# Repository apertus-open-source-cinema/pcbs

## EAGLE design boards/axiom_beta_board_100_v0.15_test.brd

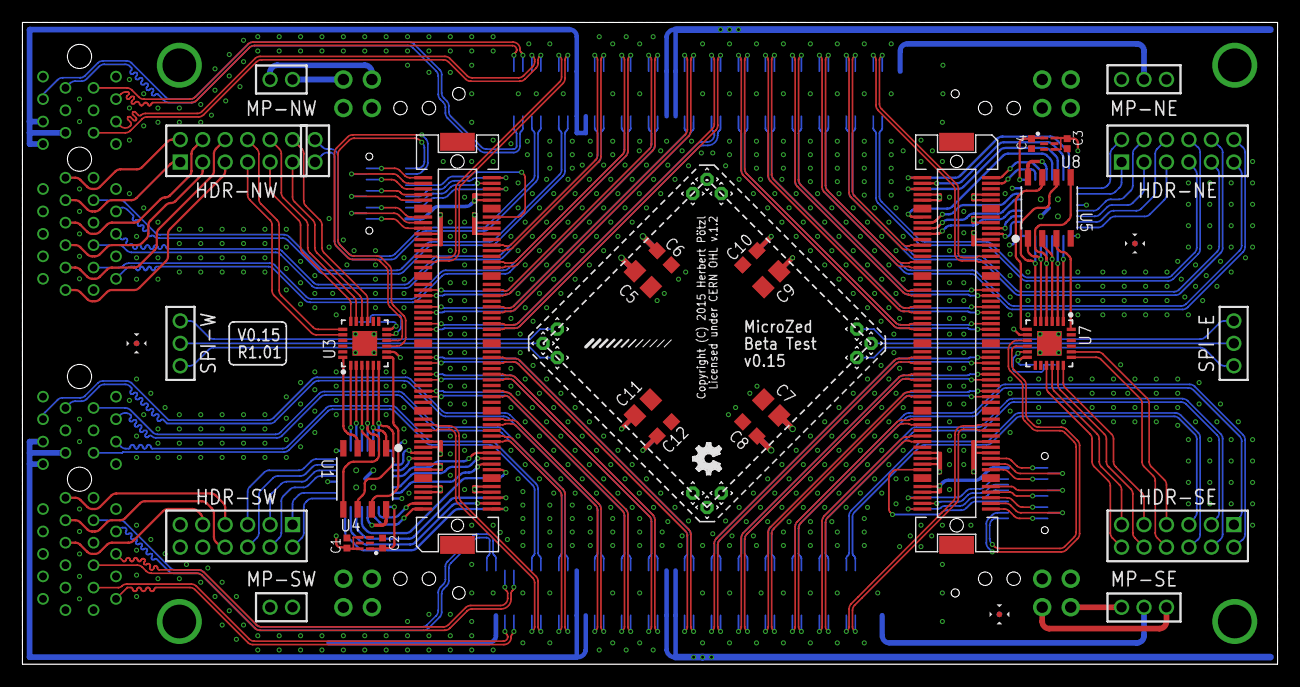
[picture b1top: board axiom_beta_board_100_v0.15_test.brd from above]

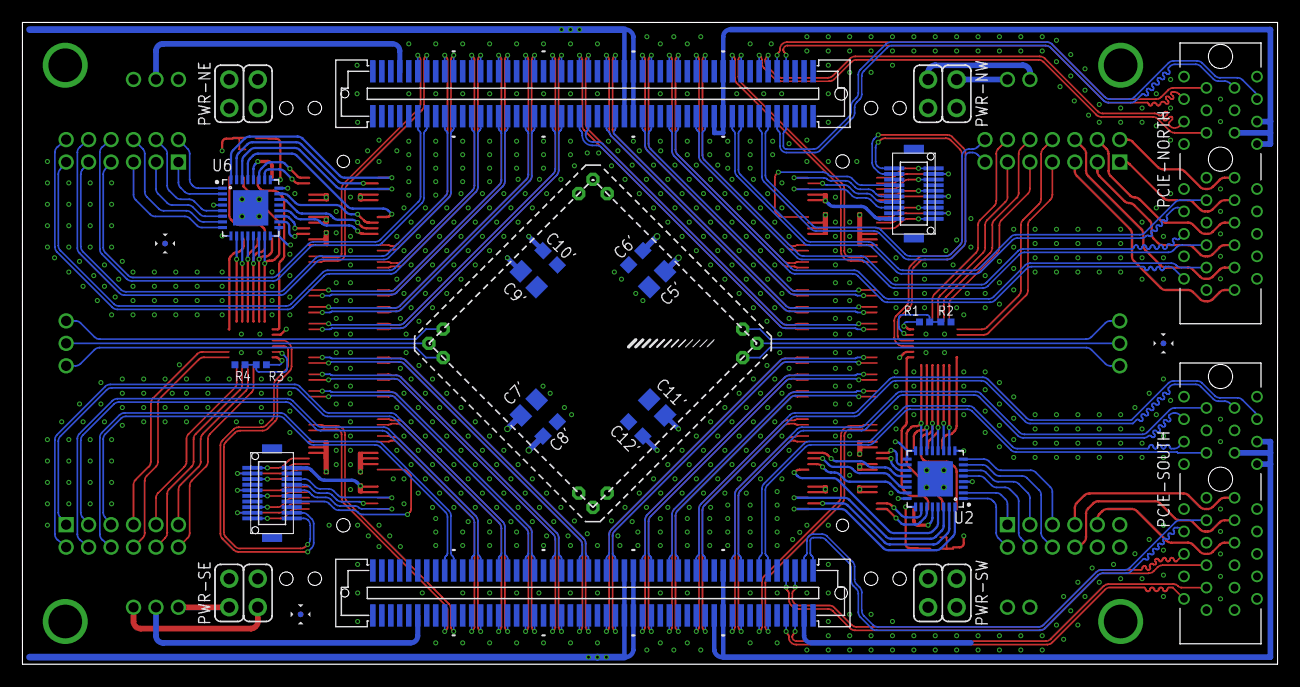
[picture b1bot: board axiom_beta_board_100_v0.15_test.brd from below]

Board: 4 copper layers, 111.8 x 57.1 mm, 67 parts (23 on the bottom side), 247 nets.

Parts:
C1, C2, C3, C4: 0402-B
C5, C5', C7, C7', C9, C9', C11, C11': 0805-A
C6, C6', C8, C8', C10, C10', C12, C12': 0603-A
HDR-NE: 2X06M
HDR-NW: 2X06M
HDR-SE: 2X06M
HDR-SW: 2X06M
LOGO1: OSHW_LOGO_FILLX0100-NT; OSHW_FILLX100_NOTEXT
M-LVDS: 1X02M
MP-NE: 1X03M
MP-NW: 1X02M
MP-SE: 1X03M
MP-SW: 1X02M
PB-NW: DF12(XX)-20DP-0.5V
PB-SE: DF12(XX)-20DP-0.5V
PCIE-NORTH: PCIE-36SOCKET; PCIE-36
PCIE-SOUTH: PCIE-36SOCKET; PCIE-36
PWR-NE: PINHD-2X02_2.54; 2X02
PWR-NW: PINHD-2X02_2.54; 2X02
PWR-SE: PINHD-2X02_2.54; 2X02
PWR-SW: PINHD-2X02_2.54; 2X02
R1, R2, R3, R4: 0402-B
SPI-E: PINHD-2X02_2.00; 1X03M
SPI-W: PINHD-2X02_2.00; 1X03M
U1, U5: SST25VF020B; SOIC127P600X175-8N
U2, U6: ICE40_LP384-SG32; QFN-32
U3, U7: MCP23018QFN; QFN50P400X400X80-25N
U4, U8: LD6806F; DFN100X150X50-6N
U$1, U$2, U$11, U$14, U$15, U$16, U$17, U$18, U$19, U$20, U$21, U$22: PINPAD1.27MM; 1.2/0.6
X-EAST: FX10-100/10S; FX10A-100S/10
X-WEST: FX10-100/10S; FX10A-100S/10
ZED1: µZ-FCI-NOHOLES; µZ-NOHOLES

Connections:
!HOLD!_N: U5.7, U7.7
!HOLD!_S: U1.7, U3.7
!WP!_N: U5.3, U7.24
!WP!_SW: U1.3, U3.24
A_SCL: PB-SE.1, U7.9
A_SDA: PB-SE.3, U7.10
BANK13_00_N: PCIE-NORTH.A14, ZED1.89
BANK13_00_P: PCIE-NORTH.A13, ZED1.87
BANK13_01_N: M-LVDS.1, ZED1.90
BANK13_01_P: M-LVDS.2, ZED1.88
BANK13_02_N: PCIE-NORTH.A16, ZED1.93
BANK13_02_P: PCIE-NORTH.A17, ZED1.91
BANK13_03_N: PCIE-NORTH.B16, ZED1.94
BANK13_03_P: PCIE-NORTH.B17, ZED1.92
BANK13_04_N: PCIE-SOUTH.A6, ZED1.195
BANK13_04_P: PCIE-SOUTH.A5, ZED1.193
BANK13_05_N: PCIE-SOUTH.A3, ZED1.196
BANK13_05_P: PCIE-SOUTH.A2, ZED1.194
BANK13_06_N: PCIE-SOUTH.A8, ZED1.199
BANK13_06_P: PCIE-SOUTH.A9, ZED1.197
B_SCL: PB-NW.1, U3.9
B_SDA: PB-NW.3, U3.10
CDONE_N: U6.11, U7.2
CDONE_S: U2.11, U3.2
CRESET_N: U6.10, U7.1
CRESET_S: U2.10, U3.1
C_CK_E: SPI-E.2, U$14.1
C_CK_W: SPI-W.2, U$1.1
C_SI_E: SPI-E.1, U$15.1
C_SI_W: SPI-W.1, U$2.1
C_SO_E: SPI-E.3, U$16.1
C_SO_W: SPI-W.3, U$11.1
E_EN: U6.23, X-EAST.14
E_I2C_V: PWR-NE.1, X-EAST.11, X-EAST.13
E_SCK: U6.29, X-EAST.12
E_SCL: U6.19, X-EAST.15
E_SDA: U6.18, X-EAST.17
E_SDI: U6.22, X-EAST.16
E_SDI_V: PWR-NE.3, X-EAST.19, X-EAST.21
E_SDO: U6.20, X-EAST.18
E_VE: PWR-SE.1, X-EAST.79, X-EAST.81, X-EAST.83, X-EAST.84, X-EAST.86, X-EAST.88
E_VE_CV: PB-SE.7, X-EAST.90
E_VE_OV: PB-SE.10, X-EAST.93
E_VE_UV: PB-SE.12, X-EAST.91
GND: C1.2, C2.2, C3.2, C4.2, C5.2, C5'.2, C6.2, C6'.2, C7.2, C7'.2, C8.2, C8'.2, C9.2, C9'.2, C10.2, C10'.2, C11.2, C11'.2, C12.2, C12'.2, MP-NE.1, MP-NE.3, MP-SW.1, MP-SW.2, PB-NW.5, PB-NW.8, PB-NW.9, PB-NW.14, PB-NW.17, PB-SE.5, PB-SE.8, PB-SE.9, PB-SE.14, PB-SE.17, PCIE-NORTH.A1, PCIE-NORTH.A4, PCIE-NORTH.A7, PCIE-NORTH.A10, PCIE-NORTH.A12, PCIE-NORTH.A15, PCIE-NORTH.A18, PCIE-NORTH.B15, PCIE-NORTH.B18, PCIE-SOUTH.A1, PCIE-SOUTH.A4, PCIE-SOUTH.A7, PCIE-SOUTH.A10, PCIE-SOUTH.A12, PCIE-SOUTH.A15, PCIE-SOUTH.A18, PCIE-SOUTH.B15, PCIE-SOUTH.B18, R2.2, R4.2, U1.4, U2.3, U2.21, U2.EP, U3.23, U4.3, U5.4, U6.3, U6.21, U6.EP, U7.23, U8.3, U$17.1, U$20.1, X-EAST.5, X-EAST.20, X-EAST.23, X-EAST.26, X-EAST.29, X-EAST.31, X-EAST.32, X-EAST.37, X-EAST.38, X-EAST.43, X-EAST.44, X-EAST.49, X-EAST.50, X-EAST.51, X-EAST.52, X-EAST.57, X-EAST.58, X-EAST.63, X-EAST.64, X-EAST.69, X-EAST.70, X-EAST.71, X-EAST.76, X-EAST.77, X-EAST.82, X-EAST.G1, X-EAST.G2, X-EAST.G3, X-EAST.G4, X-EAST.G5, X-EAST.G6, X-EAST.G7, X-EAST.G8, X-EAST.G9, X-EAST.G10, X-WEST.5, X-WEST.20, X-WEST.23, X-WEST.26, X-WEST.29, X-WEST.31, X-WEST.32, X-WEST.37, X-WEST.38, X-WEST.43, X-WEST.44, X-WEST.49, X-WEST.50, X-WEST.51, X-WEST.52, X-WEST.57, X-WEST.58, X-WEST.63, X-WEST.64, X-WEST.69, X-WEST.70, X-WEST.71, X-WEST.76, X-WEST.77, X-WEST.82, X-WEST.G1, X-WEST.G2, X-WEST.G3, X-WEST.G4, X-WEST.G5, X-WEST.G6, X-WEST.G7, X-WEST.G8, X-WEST.G9, X-WEST.G10, ZED1.15, ZED1.16, ZED1.21, ZED1.22, ZED1.27, ZED1.28, ZED1.33, ZED1.34, ZED1.39, ZED1.40, ZED1.45, ZED1.46, ZED1.51, ZED1.52, ZED1.65, ZED1.66, ZED1.71, ZED1.72, ZED1.77, ZED1.85, ZED1.86, ZED1.95, ZED1.96, ZED1.115, ZED1.116, ZED1.121, ZED1.122, ZED1.127, ZED1.128, ZED1.133, ZED1.134, ZED1.139, ZED1.140, ZED1.145, ZED1.146, ZED1.151, ZED1.152, ZED1.165, ZED1.166, ZED1.171, ZED1.172, ZED1.177, ZED1.185, ZED1.186, ZED1.191, ZED1.192
GPA0_E: HDR-SE.12, U7.15
GPA0_W: HDR-NW.12, U3.15
GPA1_E: HDR-SE.11, U7.16
GPA1_W: HDR-NW.11, U3.16
GPA2_E: HDR-SE.10, U7.17
GPA2_W: HDR-NW.10, U3.17
GPA3_E: HDR-SE.9, U7.18
GPA3_W: HDR-NW.9, U3.18
GPA4_E: HDR-SE.8, U7.19
GPA4_W: HDR-NW.8, U3.19
GPA5_E: HDR-SE.7, U7.20
GPA5_W: HDR-NW.7, U3.20
IOL_2A_N: HDR-NE.1, U6.2
IOL_2A_S: HDR-SW.1, U2.2
IOL_2B_N: HDR-NE.2, U6.1
IOL_2B_S: HDR-SW.2, U2.1
IOL_4A_N: HDR-NE.4, U6.5
IOL_4A_S: HDR-SW.4, U2.5
IOL_4B_N: HDR-NE.3, U6.6
IOL_4B_S: HDR-SW.3, U2.6
IOL_5A_N: HDR-NE.5, U6.8
IOL_5A_S: HDR-SW.5, U2.8
IOL_5B_N: HDR-NE.6, U6.7
IOL_5B_S: HDR-SW.6, U2.7
JTAG_V: PWR-SW.3, X-WEST.19, X-WEST.21
JX1_00_N: X-EAST.27, ZED1.13
JX1_00_P: X-EAST.25, ZED1.11
JX1_01_N: HDR-NE.8, ZED1.14
JX1_01_P: HDR-NE.7, ZED1.12
JX1_02_N: X-EAST.24, ZED1.19
JX1_02_P: X-EAST.22, ZED1.17
JX1_03_N: HDR-NE.10, ZED1.20
JX1_03_P: HDR-NE.9, ZED1.18
JX1_04_N: X-EAST.30, ZED1.25
JX1_04_P: X-EAST.28, ZED1.23
JX1_05_N: HDR-NE.12, ZED1.26
JX1_05_P: HDR-NE.11, ZED1.24
JX1_06_N: X-EAST.36, ZED1.31
JX1_06_P: X-EAST.34, ZED1.29
JX1_07_N: X-EAST.35, ZED1.32
JX1_07_P: X-EAST.33, ZED1.30
JX1_08_N: X-EAST.42, ZED1.37
JX1_08_P: X-EAST.40, ZED1.35
JX1_09_N: X-EAST.41, ZED1.38
JX1_09_P: X-EAST.39, ZED1.36
JX1_10_N: X-EAST.48, ZED1.43
JX1_10_P: X-EAST.46, ZED1.41
JX1_11_N: X-EAST.47, ZED1.44
JX1_11_P: X-EAST.45, ZED1.42
JX1_12_N: X-WEST.56, ZED1.49
JX1_12_P: X-WEST.54, ZED1.47
JX1_13_N: X-WEST.55, ZED1.50
JX1_13_P: X-WEST.53, ZED1.48
JX1_14_N: X-WEST.62, ZED1.55
JX1_14_P: X-WEST.60, ZED1.53
JX1_15_N: X-WEST.61, ZED1.56
JX1_15_P: X-WEST.59, ZED1.54
JX1_16_N: X-WEST.68, ZED1.63
JX1_16_P: X-WEST.66, ZED1.61
JX1_17_N: X-WEST.67, ZED1.64
JX1_17_P: X-WEST.65, ZED1.62
JX1_18_N: X-WEST.74, ZED1.69
JX1_18_P: X-WEST.72, ZED1.67
JX1_19_N: PCIE-NORTH.A3, ZED1.70
JX1_19_P: PCIE-NORTH.A2, ZED1.68
JX1_20_N: X-WEST.80, ZED1.75
JX1_20_P: X-WEST.78, ZED1.73
JX1_21_N: PCIE-NORTH.A6, ZED1.76
JX1_21_P: PCIE-NORTH.A5, ZED1.74
JX1_22_N: X-WEST.75, ZED1.83
JX1_22_P: X-WEST.73, ZED1.81
JX1_23_N: PCIE-NORTH.A9, ZED1.84
JX1_23_P: PCIE-NORTH.A8, ZED1.82
JX2_00_N: HDR-SE.6, ZED1.119
JX2_00_P: HDR-SE.5, ZED1.117
JX2_01_N: X-EAST.73, ZED1.120
JX2_01_P: X-EAST.75, ZED1.118
JX2_02_N: HDR-SE.4, ZED1.125
JX2_02_P: HDR-SE.3, ZED1.123
JX2_03_N: X-EAST.78, ZED1.126
JX2_03_P: X-EAST.80, ZED1.124
JX2_04_N: HDR-SE.2, ZED1.131
JX2_04_P: HDR-SE.1, ZED1.129
JX2_05_N: X-EAST.72, ZED1.132
JX2_05_P: X-EAST.74, ZED1.130
JX2_06_N: X-EAST.65, ZED1.137
JX2_06_P: X-EAST.67, ZED1.135
JX2_07_N: X-EAST.66, ZED1.138
JX2_07_P: X-EAST.68, ZED1.136
JX2_08_N: X-EAST.59, ZED1.143
JX2_08_P: X-EAST.61, ZED1.141
JX2_09_N: X-EAST.60, ZED1.144
JX2_09_P: X-EAST.62, ZED1.142
JX2_10_N: X-EAST.53, ZED1.149
JX2_10_P: X-EAST.55, ZED1.147
JX2_11_N: X-EAST.54, ZED1.150
JX2_11_P: X-EAST.56, ZED1.148
JX2_12_N: X-WEST.45, ZED1.155
JX2_12_P: X-WEST.47, ZED1.153
JX2_13_N: X-WEST.46, ZED1.156
JX2_13_P: X-WEST.48, ZED1.154
JX2_14_N: X-WEST.39, ZED1.163
JX2_14_P: X-WEST.41, ZED1.161
JX2_15_N: X-WEST.40, ZED1.164
JX2_15_P: X-WEST.42, ZED1.162
JX2_16_N: X-WEST.33, ZED1.169
JX2_16_P: X-WEST.35, ZED1.167
JX2_17_N: X-WEST.34, ZED1.170
JX2_17_P: X-WEST.36, ZED1.168
JX2_18_N: PCIE-SOUTH.B17, ZED1.175
JX2_18_P: PCIE-SOUTH.B16, ZED1.173
JX2_19_N: X-WEST.28, ZED1.176
JX2_19_P: X-WEST.30, ZED1.174
JX2_20_N: PCIE-SOUTH.A16, ZED1.183
JX2_20_P: PCIE-SOUTH.A17, ZED1.181
JX2_21_N: X-WEST.22, ZED1.184
JX2_21_P: X-WEST.24, ZED1.182
JX2_22_N: PCIE-SOUTH.A13, ZED1.189
JX2_22_P: PCIE-SOUTH.A14, ZED1.187
JX2_23_N: X-WEST.25, ZED1.190
JX2_23_P: X-WEST.27, ZED1.188
M_V_NW: C1.1, C5.1, C5'.1, C6.1, C6'.1, PWR-NW.3, R1.1, U1.8, U2.4, U2.9, U2.16, U2.17, U2.24, U2.28, U3.8, U3.12, U4.4, U4.6, U$18.1
M_V_SE: C3.1, C7.1, C7'.1, C8.1, C8'.1, PWR-SE.3, R3.1, U5.8, U6.4, U6.9, U6.16, U6.17, U6.24, U6.28, U7.8, U7.12, U8.4, U8.6, U$21.1
unnamed: R3.2, R4.1, U7.11
unnamed: MP-SE.2, ZED1.112
unnamed: MP-NW.1, PWR-NW.2
unnamed: MP-NW.2, PWR-NW.4
unnamed: HDR-NW.1, PCIE-NORTH.B9
unnamed: HDR-NW.3, PCIE-NORTH.B5
unnamed: HDR-NW.5, PCIE-NORTH.B1
unnamed: R1.2, R2.1, U3.11
unnamed: HDR-NW.2, PCIE-NORTH.B11
unnamed: HDR-NW.4, PCIE-NORTH.B7
unnamed: HDR-NW.6, PCIE-NORTH.B3
unnamed: MP-SE.3, PWR-SE.2
unnamed: MP-SE.1, PWR-SE.4
unnamed: HDR-SW.8, PCIE-SOUTH.B9
unnamed: HDR-SW.10, PCIE-SOUTH.B1
unnamed: HDR-SW.12, PCIE-SOUTH.B3
unnamed: HDR-SW.11, PCIE-SOUTH.B5
unnamed: HDR-SW.9, PCIE-SOUTH.B7
unnamed: HDR-SW.7, PCIE-SOUTH.B11
N_CHK_V: PB-NW.19, X-WEST.92, X-WEST.94
N_I2C_V: PWR-NE.4, X-EAST.7, X-EAST.9
N_SCK: U6.32, X-EAST.2
N_SCL: U6.27, X-EAST.1
N_SDA: U6.26, X-EAST.3
N_SDI: U6.30, X-EAST.6
N_SDO: U6.31, X-EAST.4
N_SPI_V: PWR-NE.2, X-EAST.8, X-EAST.10
N_VE_CV: PB-NW.11, X-WEST.100
N_VE_OV: PB-NW.2, X-WEST.99
N_VE_UV: PB-NW.16, X-WEST.89
N_VN_CV: PB-NW.13, X-WEST.98
N_VN_OV: PB-NW.4, X-WEST.97
N_VN_UV: PB-NW.18, X-WEST.87
N_VW_CV: PB-NW.15, X-WEST.96
N_VW_OV: PB-NW.6, X-WEST.95
N_VW_UV: PB-NW.20, X-WEST.85
PCIE_N_V: PCIE-NORTH.B12, PCIE-NORTH.B13, PCIE-NORTH.B14, ZED1.78, ZED1.79, ZED1.80
PCIE_S_V: PCIE-SOUTH.B12, PCIE-SOUTH.B13, PCIE-SOUTH.B14, ZED1.178, ZED1.179, ZED1.180
SCK_N: U5.6, U6.15, U7.6
SCK_S: U1.6, U2.15, U3.6
SDI_N: U5.5, U6.13, U7.4
SDI_S: U1.5, U2.13, U3.4
SDO_N: U5.2, U6.12, U7.3
SDO_S: U1.2, U2.12, U3.3
SS_N: U5.1, U6.14, U7.5
SS_S: U1.1, U2.14, U3.5
S_CHK_V: PB-SE.19, X-EAST.92, X-EAST.94
S_I2C_V: PWR-SW.4, X-WEST.7, X-WEST.9
S_SCK: U2.32, X-WEST.2
S_SCL: U2.27, X-WEST.1
S_SDA: U2.26, X-WEST.3
S_SDI: U2.30, X-WEST.6
S_SDO: U2.31, X-WEST.4
S_SPI_V: PWR-SW.2, X-WEST.8, X-WEST.10
S_VE_CV: PB-SE.15, X-EAST.96
S_VE_OV: PB-SE.6, X-EAST.95
S_VE_UV: PB-SE.20, X-EAST.85
S_VS_CV: PB-SE.13, X-EAST.98
S_VS_OV: PB-SE.4, X-EAST.97
S_VS_UV: PB-SE.18, X-EAST.87
S_VW_CV: PB-SE.11, X-EAST.100
S_VW_OV: PB-SE.2, X-EAST.99
S_VW_UV: PB-SE.16, X-EAST.89
TCK: U2.29, X-WEST.12
TDI: U2.22, X-WEST.16
TDO: U2.20, X-WEST.18
TMS: U2.23, X-WEST.14
V12_NW: C2.1, U2.25, U4.1
V12_SE: C4.1, U6.25, U8.1
VBAT: MP-NE.2, ZED1.7
VIN_HDR_N: C9.1, C9'.1, C10.1, C10'.1, U$19.1, ZED1.57, ZED1.58, ZED1.59, ZED1.60
VIN_HDR_S: C11.1, C11'.1, C12.1, C12'.1, U$22.1, ZED1.157, ZED1.158, ZED1.159, ZED1.160
W_I2C_V: PWR-SW.1, X-WEST.11, X-WEST.13
W_SCL: U2.19, X-WEST.15
W_SDA: U2.18, X-WEST.17
W_VW: PWR-NW.1, X-WEST.79, X-WEST.81, X-WEST.83, X-WEST.84, X-WEST.86, X-WEST.88
W_VW_CV: PB-NW.7, X-WEST.90
W_VW_OV: PB-NW.10, X-WEST.93
W_VW_UV: PB-NW.12, X-WEST.91

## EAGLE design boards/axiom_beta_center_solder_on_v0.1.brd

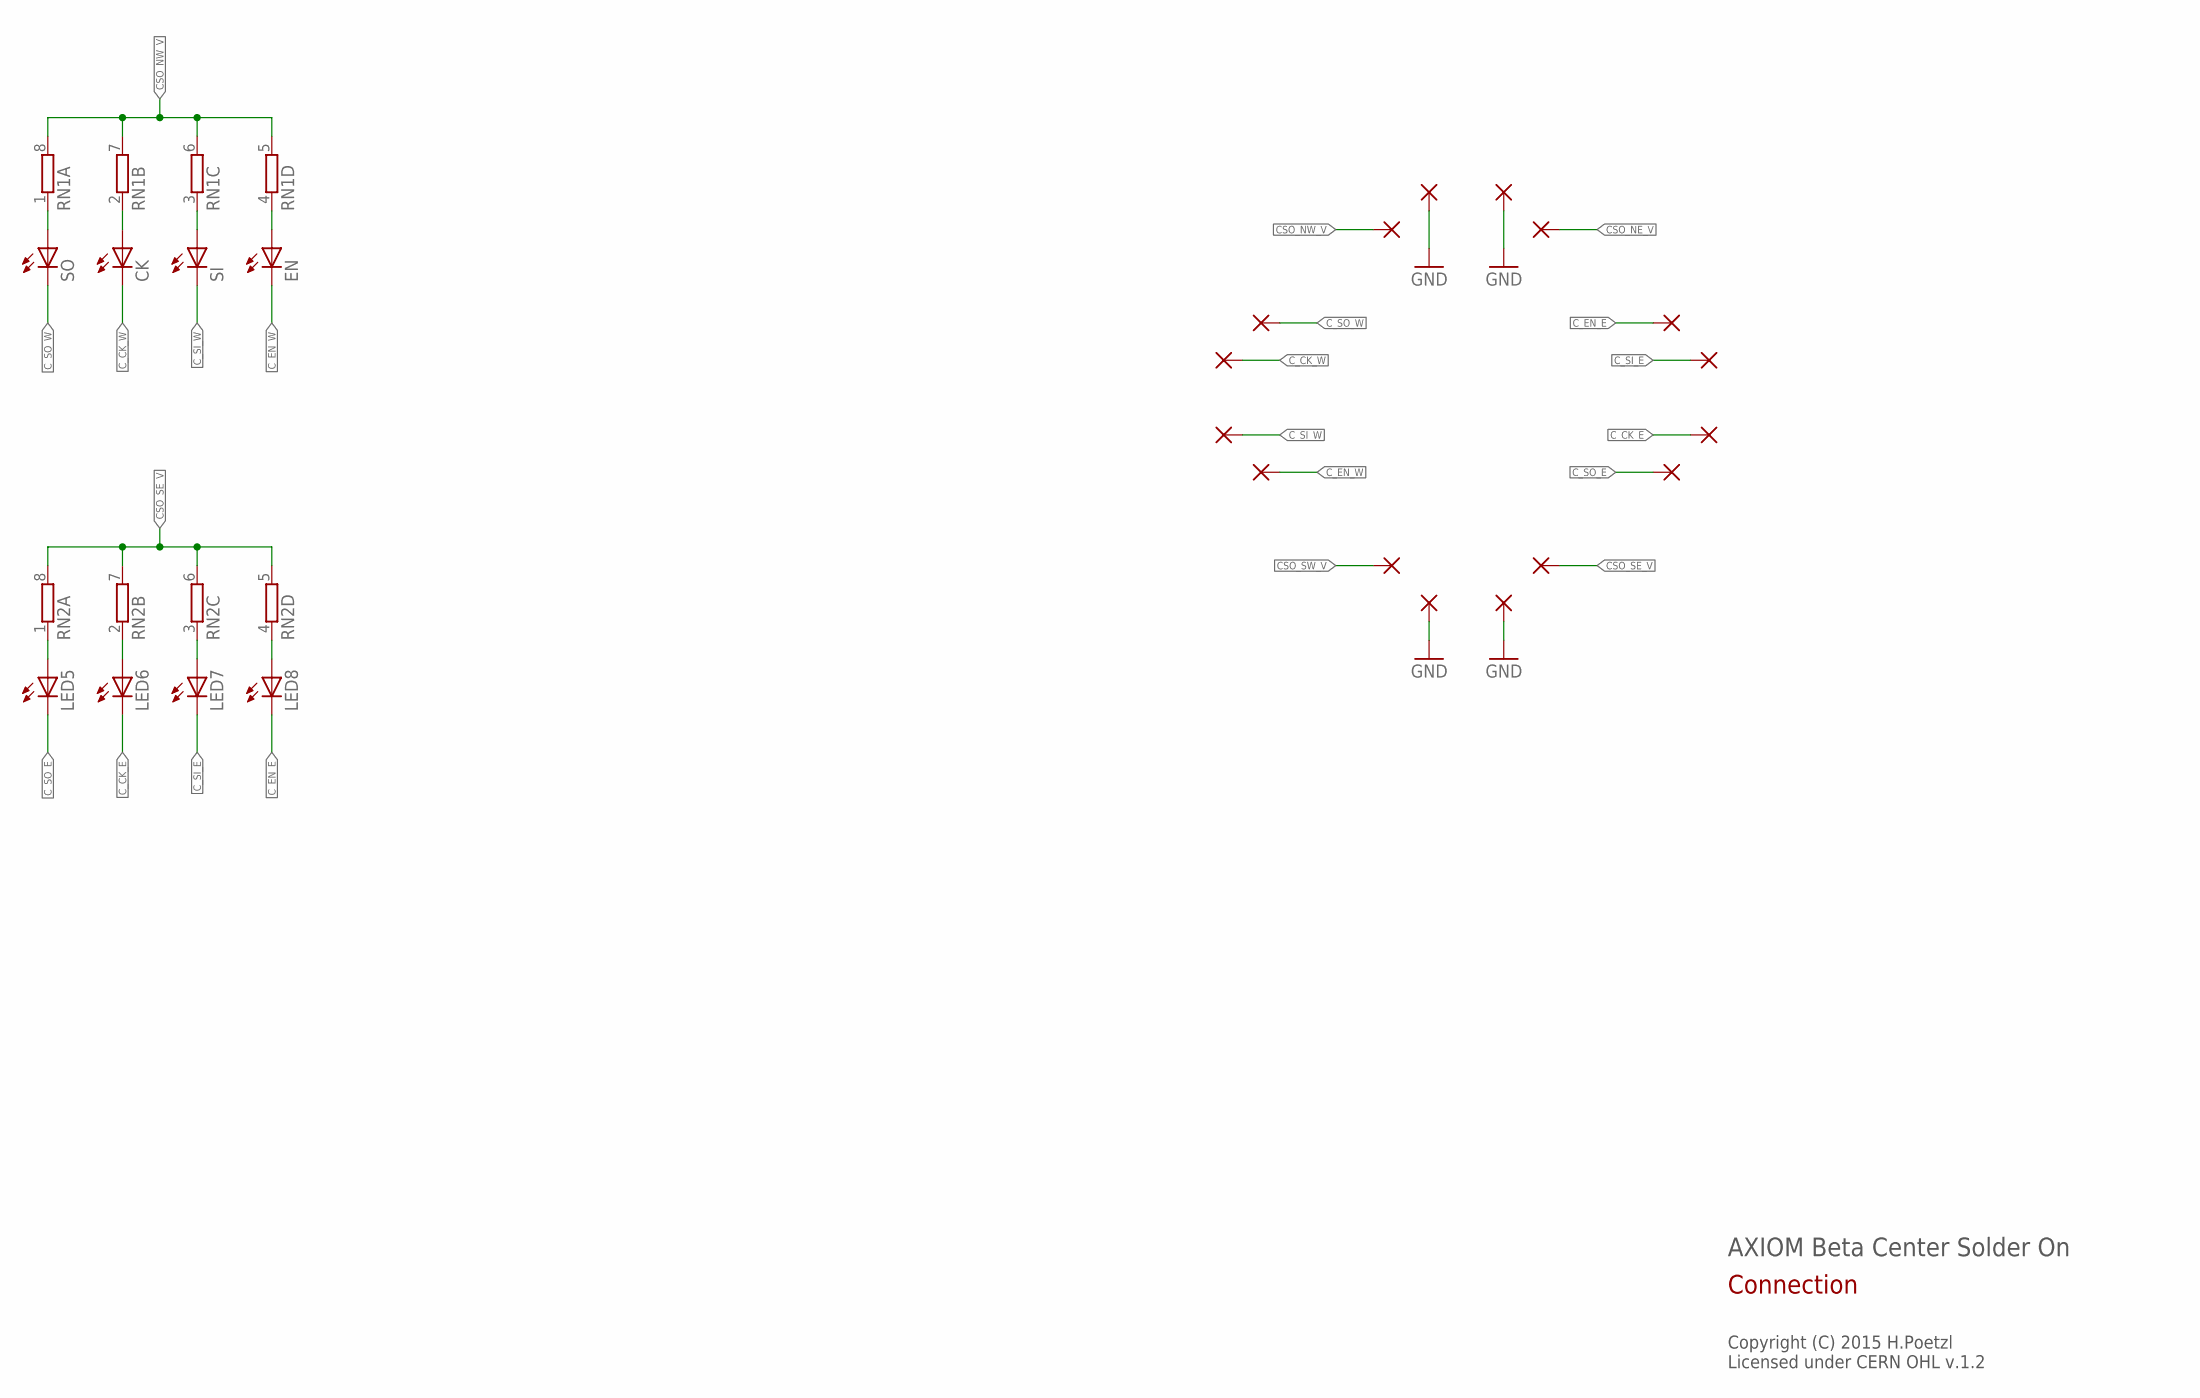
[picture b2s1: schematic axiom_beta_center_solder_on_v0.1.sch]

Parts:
CK: LEDCHIPLED_0603; CHIPLED_0603
EN: LEDCHIPLED_0603; CHIPLED_0603
LED5, LED6, LED7, LED8: LEDCHIPLED_0603; CHIPLED_0603
RN1, RN2: 4R-NCAT16; CAT16
SI: LEDCHIPLED_0603; CHIPLED_0603
SO: LEDCHIPLED_0603; CHIPLED_0603
U$1, U$2, U$3, U$4, U$5, U$6, U$11, U$14, U$15, U$16, U$17, U$18, U$19, U$20, U$21, U$22: PINPAD2.00MM; 1.4/0.8

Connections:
CSO_NE_V: U$19.1
CSO_NW_V: RN1.5 (2), RN1.6 (2), RN1.7 (2), RN1.8 (2), U$18.1
CSO_SE_V: RN2.5 (2), RN2.6 (2), RN2.7 (2), RN2.8 (2), U$21.1
CSO_SW_V: U$22.1
C_CK_E: LED6.C, U$14.1
C_CK_W: CK.C, U$1.1
C_EN_E: LED8.C, U$3.1
C_EN_W: EN.C, U$4.1
C_SI_E: LED7.C, U$15.1
C_SI_W: SI.C, U$2.1
C_SO_E: LED5.C, U$16.1
C_SO_W: SO.C, U$11.1
GND: U$5.1, U$6.1, U$17.1, U$20.1
unnamed: RN1.1, SO.A
unnamed: CK.A, RN1.2 (1)
unnamed: RN1.3 (1), SI.A
unnamed: EN.A, RN1.4 (1)
unnamed: LED5.A, RN2.1
unnamed: LED6.A, RN2.2 (1)
unnamed: LED7.A, RN2.3 (1)
unnamed: LED8.A, RN2.4 (1)

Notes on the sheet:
AXIOM Beta Center Solder On
Copyright (C) 2015 H.Poetzl Licensed under CERN OHL v.1.2
Connection

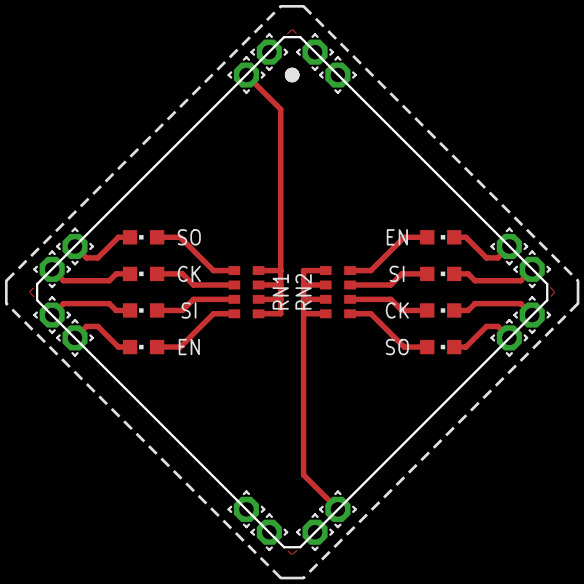
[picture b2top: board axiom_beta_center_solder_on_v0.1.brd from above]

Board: 4 copper layers, 28.3 x 28.3 mm, 27 parts (1 on the bottom side), 19 nets.

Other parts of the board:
LOGO1: OSHW_LOGO_FILLX0100-NT; OSHW_FILLX100_NOTEXT

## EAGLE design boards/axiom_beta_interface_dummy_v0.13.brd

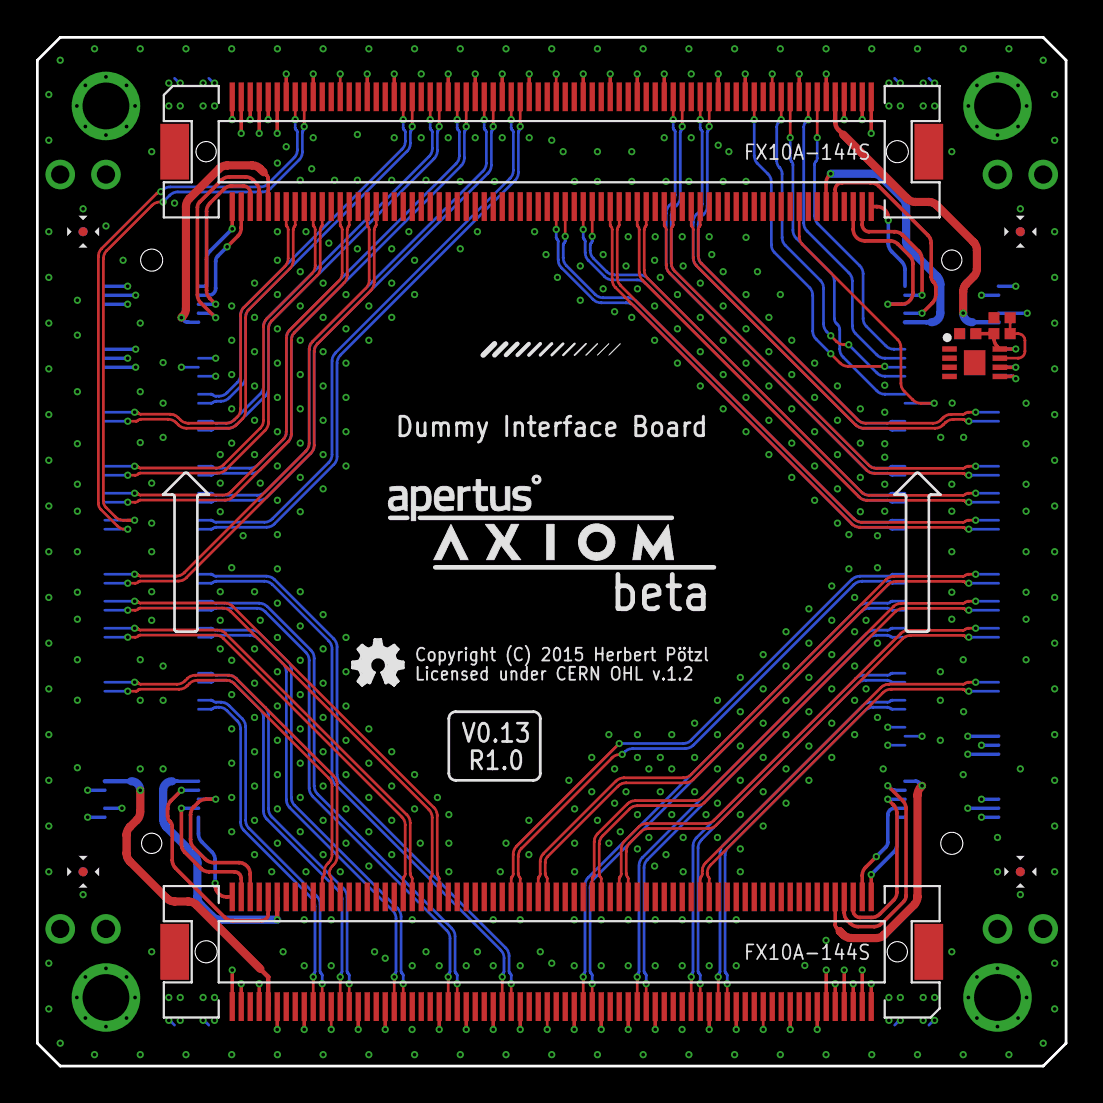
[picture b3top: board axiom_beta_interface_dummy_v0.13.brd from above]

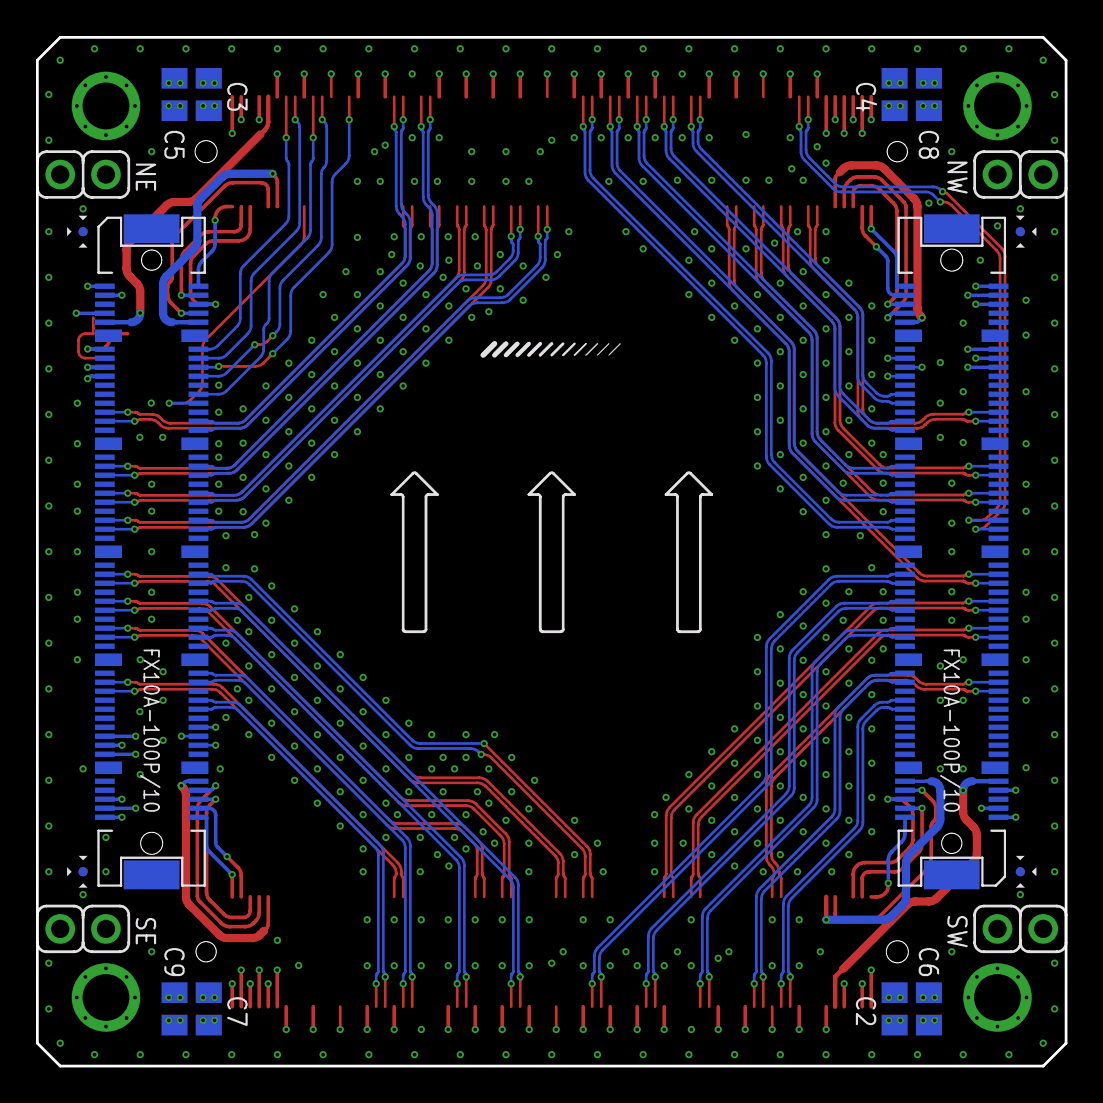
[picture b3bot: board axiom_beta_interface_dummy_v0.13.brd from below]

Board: 4 copper layers, 57.1 x 57.1 mm, 25 parts (14 on the bottom side), 135 nets.

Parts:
C1: 0402-B
C2, C3, C4, C5, C6, C7, C8, C9: 0805-B
LOGO1: OSHW_LOGO_FILLX0100-NT; OSHW_FILLX100_NOTEXT
NE: 1X02
NW: 1X02
PARALLELLA: PARALLELLA-FRAME
R1, R2: 0402-B
SE: 1X02
SW: 1X02
U1: BR24G04NUX; DFN200X300X100-9N
U$1: µZ-FRAME
U$2: APERTUS_LOGO334X100; APERTUS_LOGO_334X100
U$3: AXIOM_LOGO525X80; AXIOM_LOGO_525X80
X-EAST: FX10-100/10P; FX10A-100P/10
X-NORTH: FX10-144S; FX10A-144S
X-SOUTH: FX10-144S; FX10A-144S
X-WEST: FX10-100/10P; FX10A-100P/10

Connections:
CLK_IN: X-EAST.24, X-NORTH.128
E_I2C_V: C1.1, R1.1, U1.8, X-EAST.11
E_SCL: U1.6, X-EAST.15
E_SDA: U1.5, X-EAST.17
E_VE: C9.1, SE.2
FRAME_REQ: X-EAST.14, X-NORTH.129
GND: C1.2, C2.2, C3.2, C4.2, C5.2, C6.2, C7.2, C8.2, C9.2, R2.2, U1.1, U1.2, U1.3, U1.4, U1.EP, X-EAST.5, X-EAST.20, X-EAST.23, X-EAST.26, X-EAST.29, X-EAST.31, X-EAST.32, X-EAST.37, X-EAST.38, X-EAST.43, X-EAST.44, X-EAST.49, X-EAST.50, X-EAST.51, X-EAST.52, X-EAST.57, X-EAST.58, X-EAST.63, X-EAST.64, X-EAST.69, X-EAST.70, X-EAST.71, X-EAST.76, X-EAST.77, X-EAST.82, X-EAST.G1, X-EAST.G2, X-EAST.G3, X-EAST.G4, X-EAST.G5, X-EAST.G6, X-EAST.G7, X-EAST.G8, X-EAST.G9, X-EAST.G10, X-NORTH.12, X-NORTH.18, X-NORTH.24, X-NORTH.30, X-NORTH.36, X-NORTH.42, X-NORTH.43, X-NORTH.48, X-NORTH.54, X-NORTH.60, X-NORTH.66, X-NORTH.72, X-NORTH.78, X-NORTH.84, X-NORTH.90, X-NORTH.96, X-NORTH.102, X-NORTH.103, X-NORTH.108, X-NORTH.114, X-NORTH.120, X-NORTH.126, X-NORTH.132, X-NORTH.138, X-NORTH.139, X-SOUTH.12, X-SOUTH.18, X-SOUTH.24, X-SOUTH.30, X-SOUTH.36, X-SOUTH.42, X-SOUTH.43, X-SOUTH.48, X-SOUTH.54, X-SOUTH.60, X-SOUTH.66, X-SOUTH.72, X-SOUTH.78, X-SOUTH.84, X-SOUTH.90, X-SOUTH.96, X-SOUTH.102, X-SOUTH.103, X-SOUTH.108, X-SOUTH.114, X-SOUTH.120, X-SOUTH.126, X-SOUTH.132, X-SOUTH.138, X-SOUTH.139, X-WEST.5, X-WEST.20, X-WEST.23, X-WEST.26, X-WEST.29, X-WEST.31, X-WEST.32, X-WEST.37, X-WEST.38, X-WEST.43, X-WEST.44, X-WEST.49, X-WEST.50, X-WEST.51, X-WEST.52, X-WEST.57, X-WEST.58, X-WEST.63, X-WEST.64, X-WEST.69, X-WEST.70, X-WEST.71, X-WEST.76, X-WEST.77, X-WEST.82, X-WEST.G1, X-WEST.G2, X-WEST.G3, X-WEST.G4, X-WEST.G5, X-WEST.G6, X-WEST.G7, X-WEST.G8, X-WEST.G9, X-WEST.G10
LVDS_CLK_N: X-NORTH.14, X-WEST.75
LVDS_CLK_P: X-NORTH.16, X-WEST.73
unnamed: R1.2, R2.1, U1.7
N_CHK_EN: X-NORTH.8, X-WEST.94
N_CHK_V: X-NORTH.10, X-WEST.92
N_I2C_EN: X-EAST.7, X-NORTH.137
N_I2C_V: X-EAST.9, X-NORTH.135
N_SCK: X-EAST.2, X-NORTH.144
N_SCL: X-EAST.1, X-NORTH.143
N_SDA: X-EAST.3, X-NORTH.141
N_SDI: X-EAST.6, X-NORTH.140
N_SDO: X-EAST.4, X-NORTH.142
N_SPI_EN: X-EAST.8, X-NORTH.136
N_SPI_V: X-EAST.10, X-NORTH.134
N_VE: C5.1, NE.2, X-NORTH.109, X-NORTH.115, X-NORTH.127, X-NORTH.133
N_VE_CV: X-NORTH.6, X-WEST.96
N_VE_OV: X-NORTH.5, X-WEST.95
N_VE_RS: X-NORTH.121, X-WEST.88
N_VE_UV: X-NORTH.11, X-WEST.85
N_VN: C3.1, NE.1, X-NORTH.49, X-NORTH.55, X-NORTH.61, X-NORTH.67, X-NORTH.79, X-NORTH.85, X-NORTH.91, X-NORTH.97
N_VN_CV: X-NORTH.4, X-WEST.98
N_VN_OV: X-NORTH.3, X-WEST.97
N_VN_RS: X-NORTH.73, X-WEST.86
N_VN_UV: X-NORTH.9, X-WEST.87
N_VW: C4.1, NW.1, X-NORTH.13, X-NORTH.19, X-NORTH.31, X-NORTH.37
N_VW_CV: X-NORTH.2, X-WEST.100
N_VW_OV: X-NORTH.1, X-WEST.99
N_VW_RS: X-NORTH.25, X-WEST.84
N_VW_UV: X-NORTH.7, X-WEST.89
OUT1_N: X-SOUTH.119, X-WEST.28
OUT1_P: X-SOUTH.117, X-WEST.30
OUT3_N: X-SOUTH.124, X-WEST.25
OUT3_P: X-SOUTH.122, X-WEST.27
OUT5_N: X-SOUTH.107, X-WEST.34
OUT5_P: X-SOUTH.105, X-WEST.36
OUT7_N: X-SOUTH.106, X-WEST.33
OUT7_P: X-SOUTH.104, X-WEST.35
OUT9_N: X-SOUTH.95, X-WEST.40
OUT9_P: X-SOUTH.93, X-WEST.42
OUT11_N: X-SOUTH.100, X-WEST.39
OUT11_P: X-SOUTH.98, X-WEST.41
OUT13_N: X-SOUTH.83, X-WEST.46
OUT13_P: X-SOUTH.81, X-WEST.48
OUT15_N: X-EAST.54, X-SOUTH.82
OUT15_P: X-EAST.56, X-SOUTH.80
OUT17_N: X-EAST.53, X-SOUTH.76
OUT17_P: X-EAST.55, X-SOUTH.74
OUT19_N: X-EAST.60, X-SOUTH.65
OUT19_P: X-EAST.62, X-SOUTH.63
OUT21_N: X-EAST.59, X-SOUTH.64
OUT21_P: X-EAST.61, X-SOUTH.62
OUT23_N: X-EAST.66, X-SOUTH.53
OUT23_P: X-EAST.68, X-SOUTH.51
OUT25_N: X-EAST.65, X-SOUTH.58
OUT25_P: X-EAST.67, X-SOUTH.56
OUT27_N: X-EAST.73, X-SOUTH.40
OUT27_P: X-EAST.75, X-SOUTH.38
OUT29_N: X-EAST.72, X-SOUTH.41
OUT29_P: X-EAST.74, X-SOUTH.39
OUT31_N: X-EAST.78, X-SOUTH.35
OUT31_P: X-EAST.80, X-SOUTH.33
OUT33_N: X-NORTH.20, X-WEST.67
OUT33_P: X-NORTH.22, X-WEST.65
OUT35_N: X-NORTH.26, X-WEST.61
OUT35_P: X-NORTH.28, X-WEST.59
OUT37_N: X-NORTH.32, X-WEST.47
OUT37_P: X-NORTH.34, X-WEST.45
OUT39_N: X-NORTH.39, X-WEST.80
OUT39_P: X-NORTH.41, X-WEST.78
OUT41_N: X-NORTH.45, X-WEST.74
OUT41_P: X-NORTH.47, X-WEST.72
OUT43_N: X-NORTH.51, X-WEST.68
OUT43_P: X-NORTH.53, X-WEST.66
OUT45_N: X-NORTH.57, X-WEST.62
OUT45_P: X-NORTH.59, X-WEST.60
OUT47_N: X-NORTH.63, X-WEST.56
OUT47_P: X-NORTH.65, X-WEST.54
OUT49_N: X-EAST.48, X-NORTH.74
OUT49_P: X-EAST.46, X-NORTH.76
OUT51_N: X-EAST.42, X-NORTH.80
OUT51_P: X-EAST.40, X-NORTH.82
OUT53_N: X-EAST.47, X-NORTH.86
OUT53_P: X-EAST.45, X-NORTH.88
OUT55_N: X-EAST.41, X-NORTH.92
OUT55_P: X-EAST.39, X-NORTH.94
OUT57_N: X-EAST.35, X-NORTH.98
OUT57_P: X-EAST.33, X-NORTH.100
OUT59_N: X-EAST.27, X-NORTH.104
OUT59_P: X-EAST.25, X-NORTH.106
OUT61_N: X-EAST.36, X-NORTH.99
OUT61_P: X-EAST.34, X-NORTH.101
OUT63_N: X-EAST.30, X-NORTH.105
OUT63_P: X-EAST.28, X-NORTH.107
OUTCLK_N: X-NORTH.15, X-WEST.53
OUTCLK_P: X-NORTH.17, X-WEST.55
OUTCTR_N: X-SOUTH.125, X-WEST.22
OUTCTR_P: X-SOUTH.123, X-WEST.24
SYS_RES_N: X-EAST.22, X-NORTH.125
S_CHK_EN: X-EAST.94, X-SOUTH.8
S_CHK_V: X-EAST.92, X-SOUTH.10
S_I2C_EN: X-SOUTH.137, X-WEST.7
S_I2C_V: X-SOUTH.135, X-WEST.9
S_SCK: X-SOUTH.144, X-WEST.2
S_SCL: X-SOUTH.143, X-WEST.1
S_SDA: X-SOUTH.141, X-WEST.3
S_SDI: X-SOUTH.140, X-WEST.6
S_SDO: X-SOUTH.142, X-WEST.4
S_SPI_EN: X-SOUTH.136, X-WEST.8
S_SPI_V: X-SOUTH.134, X-WEST.10
S_VE: C7.1, SE.1, X-SOUTH.13, X-SOUTH.19, X-SOUTH.31, X-SOUTH.37
S_VE_CV: X-EAST.100, X-SOUTH.2
S_VE_OV: X-EAST.99, X-SOUTH.1
S_VE_RS: X-EAST.84, X-SOUTH.25
S_VE_UV: X-EAST.89, X-SOUTH.7
S_VS: C6.1, SW.1, X-SOUTH.49, X-SOUTH.55, X-SOUTH.61, X-SOUTH.67, X-SOUTH.79, X-SOUTH.85, X-SOUTH.91, X-SOUTH.97
S_VS_CV: X-EAST.98, X-SOUTH.4
S_VS_OV: X-EAST.97, X-SOUTH.3
S_VS_RS: X-EAST.86, X-SOUTH.73
S_VS_UV: X-EAST.87, X-SOUTH.9
S_VW: C2.1, SW.2, X-SOUTH.109, X-SOUTH.115, X-SOUTH.127, X-SOUTH.133
S_VW_CV: X-EAST.96, X-SOUTH.6
S_VW_OV: X-EAST.95, X-SOUTH.5
S_VW_RS: X-EAST.88, X-SOUTH.121
S_VW_UV: X-EAST.85, X-SOUTH.11
TDIG1: X-EAST.18, X-NORTH.123
T_EXP1: X-EAST.12, X-NORTH.131
T_EXP2: X-EAST.16, X-NORTH.117
W_VW: C8.1, NW.2

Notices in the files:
boards/axiom_beta_board_100_v0.15_test.brd:
Copyright (C) 2015 Herbert Pötzl
boards/axiom_beta_center_solder_on_v0.1.brd:
Copyright (C) 2016 Herbert Pötzl
